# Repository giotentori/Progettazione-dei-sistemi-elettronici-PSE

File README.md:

# Progettazione-dei-sistemi-elettronici-PSE
Progetto e relazione per il corso di progettazione dei sistemi elettronici
Progetto sul componente Timer 555

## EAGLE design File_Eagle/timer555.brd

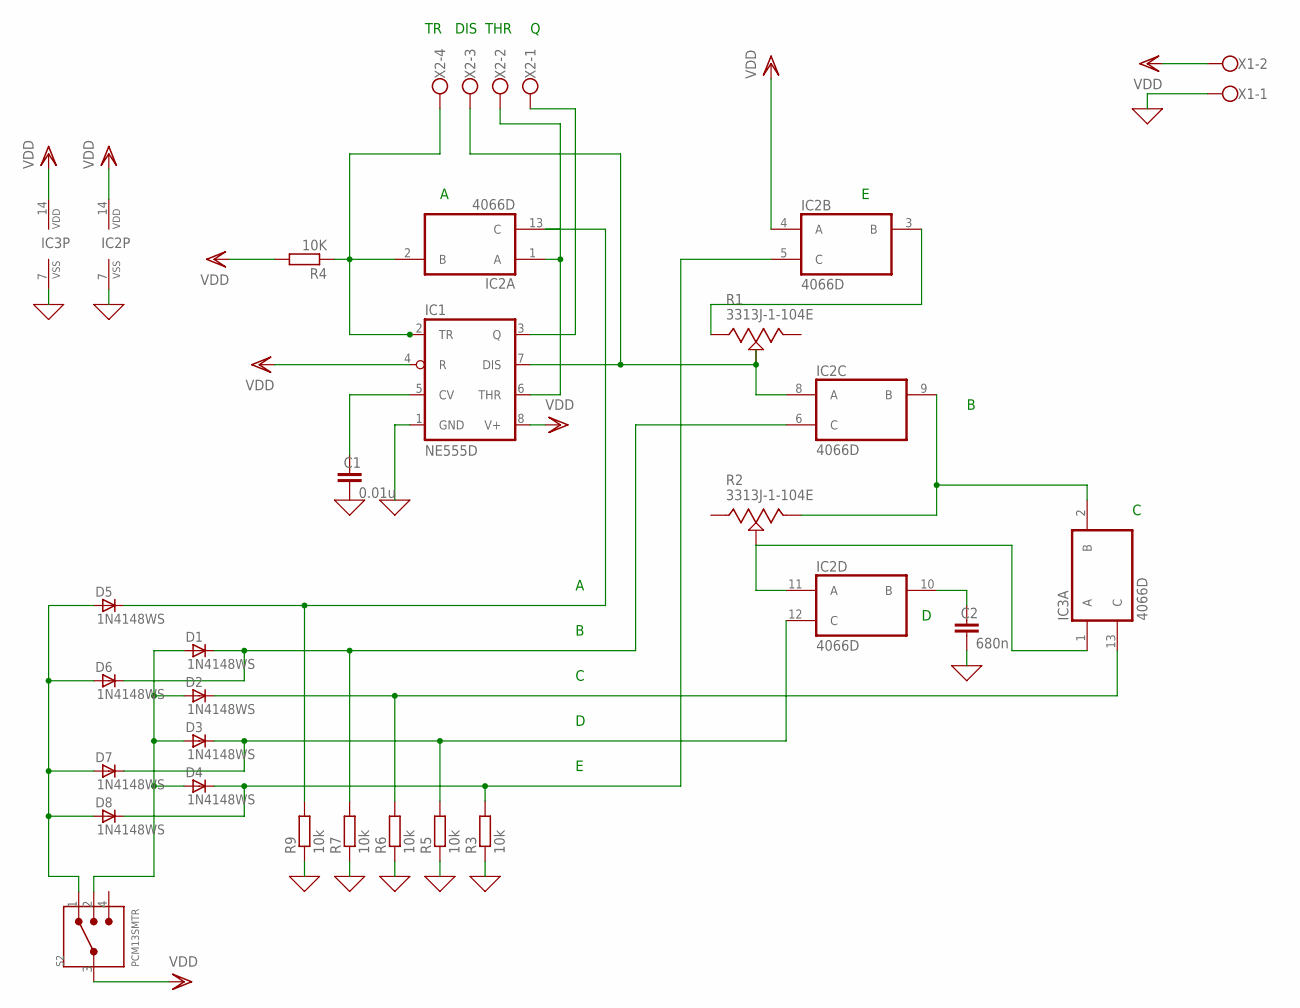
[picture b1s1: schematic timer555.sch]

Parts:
C1: 0.01u; C0805
C2: 680n; C0805
D1, D2, D3, D4, D5, D6, D7, D8: 1N4148WS; SOD323F
IC1: NE555D; SO08
IC2, IC3: 4066D; SO14
R1, R2: 3313J-1-104E; TRIM_3313J-1-104E
R3, R5, R6, R7, R9: 10k; R0805
R4: 10K; R0805
S2: PCM13SMTR; SW_PCM13SMTR
X1: W237-102
X2: W237-4

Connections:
0: C1.2, C2.2, IC1.1 (GND), IC2.7 (VSS), IC3.7 (VSS), R3.1, R5.1, R6.1, R7.1, R9.1, X1.1
unnamed: C1.1, IC1.5 (CV)
unnamed: IC1.2 (TR), IC2.2 (B), R4.1, X2.4
unnamed: D2.C, IC3.13 (C), R6.2
unnamed: IC2.3 (B), R1.1 (CCW)
unnamed: IC1.7 (DIS), IC2.8 (A), R1.2 (WIPER), X2.3
unnamed: IC2.9 (B), IC3.2 (B), R2.3 (CW)
unnamed: IC2.11 (A), IC3.1 (A), R2.2 (WIPER)
unnamed: C2.1, IC2.10 (B)
unnamed: D1.C, D6.C, IC2.6 (C), R7.2
unnamed: D5.C, IC2.13 (C), R9.2
unnamed: IC1.3 (Q), X2.1
unnamed: D3.C, D7.C, IC2.12 (C), R5.2
unnamed: D4.C, D8.C, IC2.5 (C), R3.2
unnamed: D1.A, D2.A, D3.A, D4.A, S2.2
unnamed: IC1.6 (THR), IC2.1 (A), X2.2
unnamed: D5.A, D6.A, D7.A, D8.A, S2.1
VDD: IC1.4 (R), IC1.8 (V+), IC2.4 (A), IC2.14 (VDD), IC3.14 (VDD), R4.2, S2.3, X1.2

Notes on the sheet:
DIS
THR

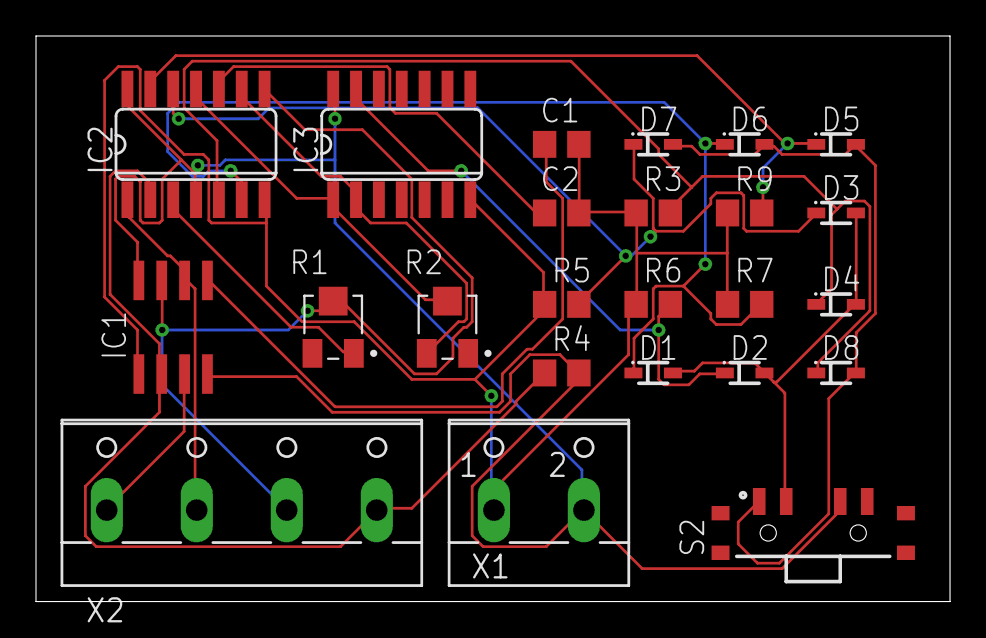
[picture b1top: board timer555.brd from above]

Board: 2 copper layers, 50.8 x 31.4 mm, 24 parts (0 on the bottom side), 18 nets.

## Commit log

2024-05-28 init
